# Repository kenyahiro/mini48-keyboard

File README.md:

# このキーボードについて
このキーボードは 19mmピッチ 48キーのロープロファイルキーボードです。
キースイッチは [kailh choc V1用ソケット](https://www.kailhswitch.com/mechanical-keyboard-switches/box-switches/choc-type-hot-swap-socket.html) を使用します。

マイコンには [AE-RP2040](https://akizukidenshi.com/catalog/g/g117542/) を使用します。

ファームウェアは [kmk_firmware](https://github.com/KMKfw/kmk_firmware) を使います。

# 部品表

| レフデス      | 型名           | 数量   | 備考 |
|------------|--------------|------|---------------------------|
| D1 - D48   | 1N4148W      | 48   |                           |
| SW1 - SW48 | CPG135001S30 | 48   | Choc Type Hot Swap Socket |
| U1         | AE-RP2040    | 1    | RP2040マイコンボード            |

この他に, kailh choc V1キースイッチ、 choc V1用キーキャップが必要です。
また、 基板を固定するためM2の支柱とネジを使います。

# マイコンの動作確認
組み立ての前にマイコンボードの動作確認を行います。
マイコンボードに [CircuitPython](https://circuitpython.org/board/raspberry_pi_pico/) を書き込みます。

書き込み後、 [Thonny](https://thonny.org/)等でCircuitPythonが動いていることを確認します。

# 組み立て

## ダイオードのハンダ付け
はじめに, D1 - D48 のダイオードをハンダ付けします。
アノードとカソードの向きを間違えないように注意してください。

## キーソケットのハンダ付け
次にkailh choc V1用キーソケットをハンダ付けします。
キーソケットには向きがあります。 基板のシルクを参考にして、間違えないようにハンダ付けしてください。

## マイコンボードの取り付け
マイコンボードの取り付け方法は、直付け または ピンソケット の選択ができます。

直付けの場合、キーボード裏の厚みを薄くできます。しかし、マイコンボードが故障したときに交換が難しくなります。

ピンソケットを使用した場合、キーボード裏の厚みがピンソケット分増加します。マイコンボードの交換は容易です。

### マイコンボードの組み立て

マイコンボードに 細ピンヘッダ(AE-RP2040付属) または [基板用リードフレーム](https://akizukidenshi.com/catalog/g/g114883/) をハンダ付けします。

細ピンヘッダをハンダ付けする場合、 ブレッドボードを使うとハンダ付けしやすいです。

リードフレームをハンダ付けする場合、 垂直になるようにハンダ付けします。まず1ピンだけ仮止めして、角度を調整します。
垂直になったら、残りのピンをハンダ付けします。

念のため、マイコンボードの裏側に[ポリイミドテープ](https://akizukidenshi.com/catalog/r/rpolyimid/)を貼って絶縁します。

### マイコンボードの取り付け(直付けの場合)
マイコンボードの取り付け前に、ダイオードとキーソケットの向き、ハンダ不良が無いことを確認します。
特に、 マイコンボードの下になる D35, D36, SW35, SW36 は注意して確認します。

U1のスルーホールにマイコンボードを刺し込みます。マイコンボードの裏側とダイオード、キーソケットが接触していないことを確認します。

マイコンボードのハンダ付けをします。まず、1つのピンをハンダ付けして仮止めします。
マイコンボードが水平になっていることを確認します。水平でない場合、ハンダゴデで仮止めしたピンのハンダを温めて、水平になるように修正します。

仮止めでマイコンボードが水平になっていることを確認できたら、残りのピンをハンダ付けします。

### マイコンボードの取り付け(ソケットの場合)
[ピンソケット](https://akizukidenshi.com/catalog/g/g100241/)はマイコンボードのピン数に合せてカットします。

基板にピンソケットをハンダ付けします。ピンソケットは垂直になるようにハンダ付けします。まず1ピンだけ仮止めして、角度を調整します。
垂直になったら、残りのピンをハンダ付けします。

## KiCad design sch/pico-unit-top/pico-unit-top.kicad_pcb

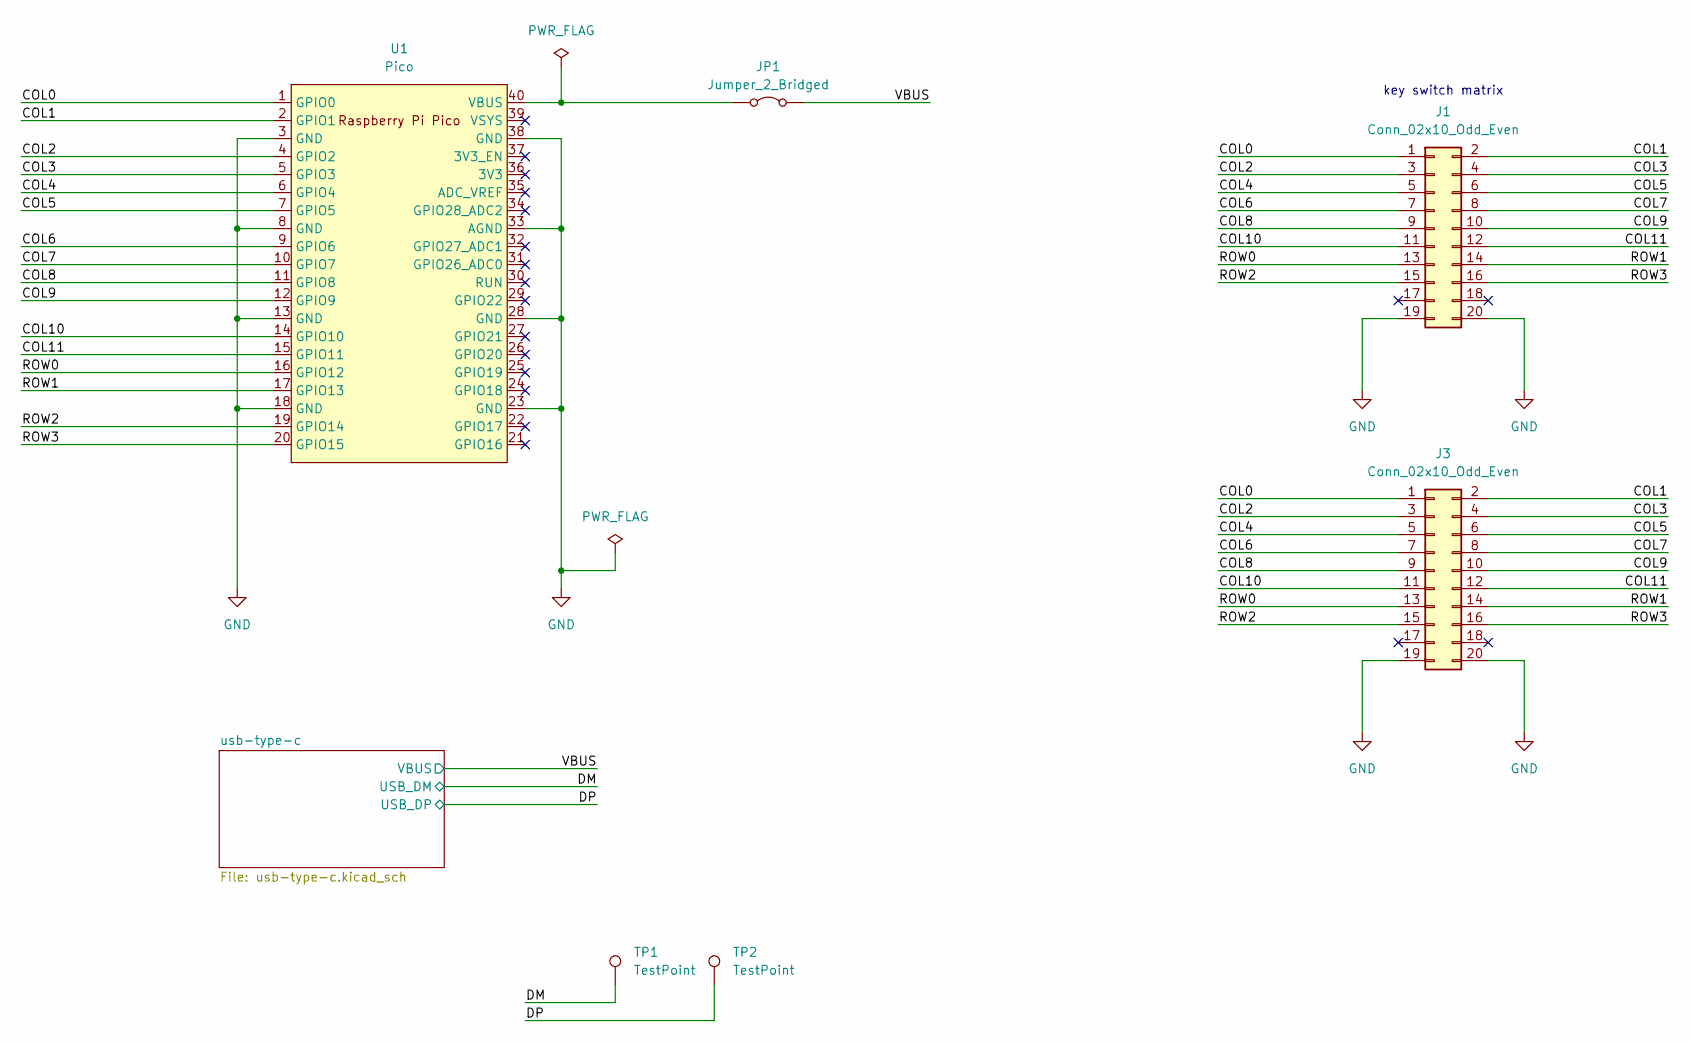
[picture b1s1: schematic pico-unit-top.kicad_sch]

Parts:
J1: Conn_02x10_Odd_Even; PinSocket_2x10_P2.54mm_Horizontal
J3: Conn_02x10_Odd_Even; PinSocket_2x10_P2.54mm_Vertical
JP1: Jumper_2_Bridged; SolderJumper-2_P1.3mm_Bridged_RoundedPad1.0x1.5mm
TP1, TP2: TestPoint; TestPoint_THTPad_2.0x2.0mm_Drill1.0mm
U1: Pico; pico_no_dbg_smd_th_p0.85

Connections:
/COL0: J1.1, J3.1, U1.1 (GPIO0)
/COL1: J1.2, J3.2, U1.2 (GPIO1)
/COL2: J1.3, J3.3, U1.4 (GPIO2)
/COL3: J1.4, J3.4, U1.5 (GPIO3)
/COL4: J1.5, J3.5, U1.6 (GPIO4)
/COL5: J1.6, J3.6, U1.7 (GPIO5)
/COL6: J1.7, J3.7, U1.9 (GPIO6)
/COL7: J1.8, J3.8, U1.10 (GPIO7)
/COL8: J1.9, J3.9, U1.11 (GPIO8)
/COL9: J1.10, J3.10, U1.12 (GPIO9)
/COL10: J1.11, J3.11, U1.14 (GPIO10)
/COL11: J1.12, J3.12, U1.15 (GPIO11)
/DM: TP1.1; also elsewhere on the board
/DP: TP2.1; also elsewhere on the board
/ROW0: J1.13, J3.13, U1.16 (GPIO12)
/ROW1: J1.14, J3.14, U1.17 (GPIO13)
/ROW2: J1.15, J3.15, U1.19 (GPIO14)
/ROW3: J1.16, J3.16, U1.20 (GPIO15)
/VBUS: JP1.2 (B); also elsewhere on the board
GND: J1.19, J1.20, J3.19, J3.20, U1.3 (GND), U1.8 (GND), U1.13 (GND), U1.18 (GND), U1.23 (GND), U1.28 (GND), U1.33 (AGND), U1.38 (GND); also elsewhere on the board
unnamed: JP1.1 (A), U1.40 (VBUS)

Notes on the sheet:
key switch matrix

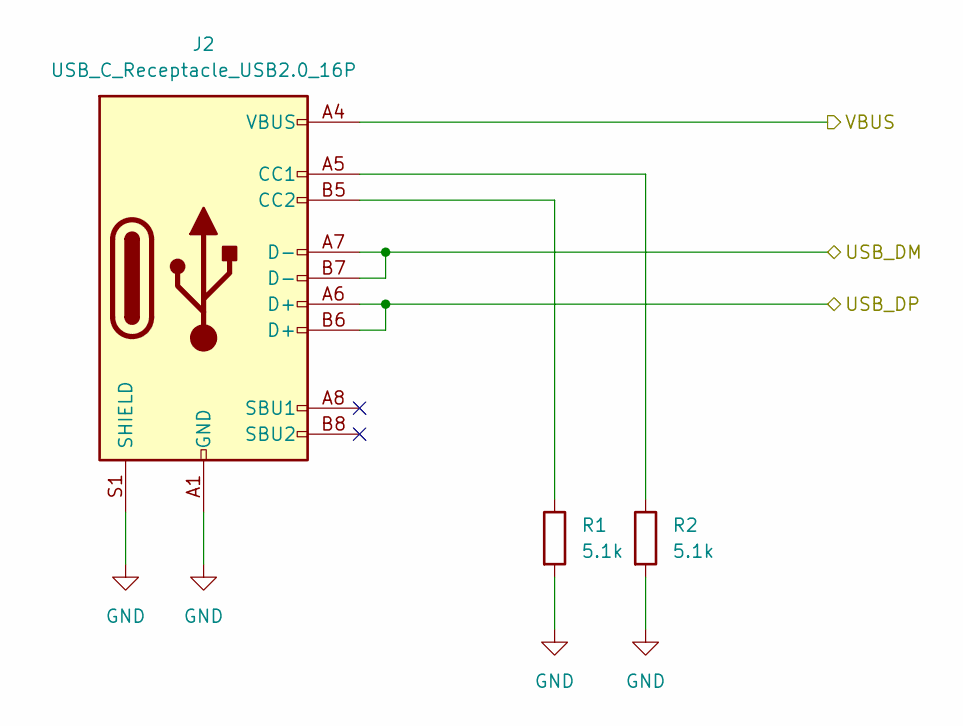
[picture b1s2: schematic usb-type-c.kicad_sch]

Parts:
J2: USB_C_Receptacle_USB2.0_16P; USB_C_Receptacle_G-Switch_GT-USB-7010ASV
R1, R2: 5.1k; R_0603_1608Metric

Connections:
/DM: J2.A7 (D-), J2.B7 (D-); also elsewhere on the board
/DP: J2.A6 (D+), J2.B6 (D+); also elsewhere on the board
/VBUS: J2.A4 (VBUS), J2.A9 (VBUS), J2.B4 (VBUS), J2.B9 (VBUS); also elsewhere on the board
GND: J2.A1 (GND), J2.A12 (GND), J2.B1 (GND), J2.B12 (GND), J2.S1 (SHIELD), R1.2, R2.2; also elsewhere on the board
unnamed: J2.A5 (CC1), R2.1
unnamed: J2.B5 (CC2), R1.1

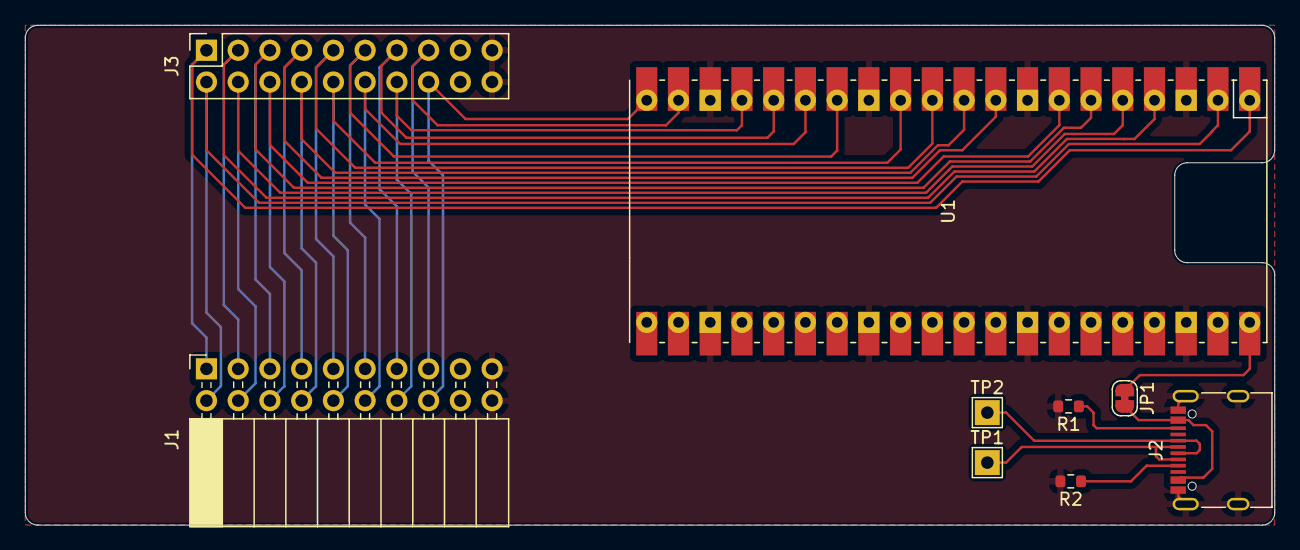
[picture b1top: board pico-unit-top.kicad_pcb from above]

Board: 2 copper layers, 100.0 x 40.0 mm, 9 parts (0 on the bottom side), 23 nets.

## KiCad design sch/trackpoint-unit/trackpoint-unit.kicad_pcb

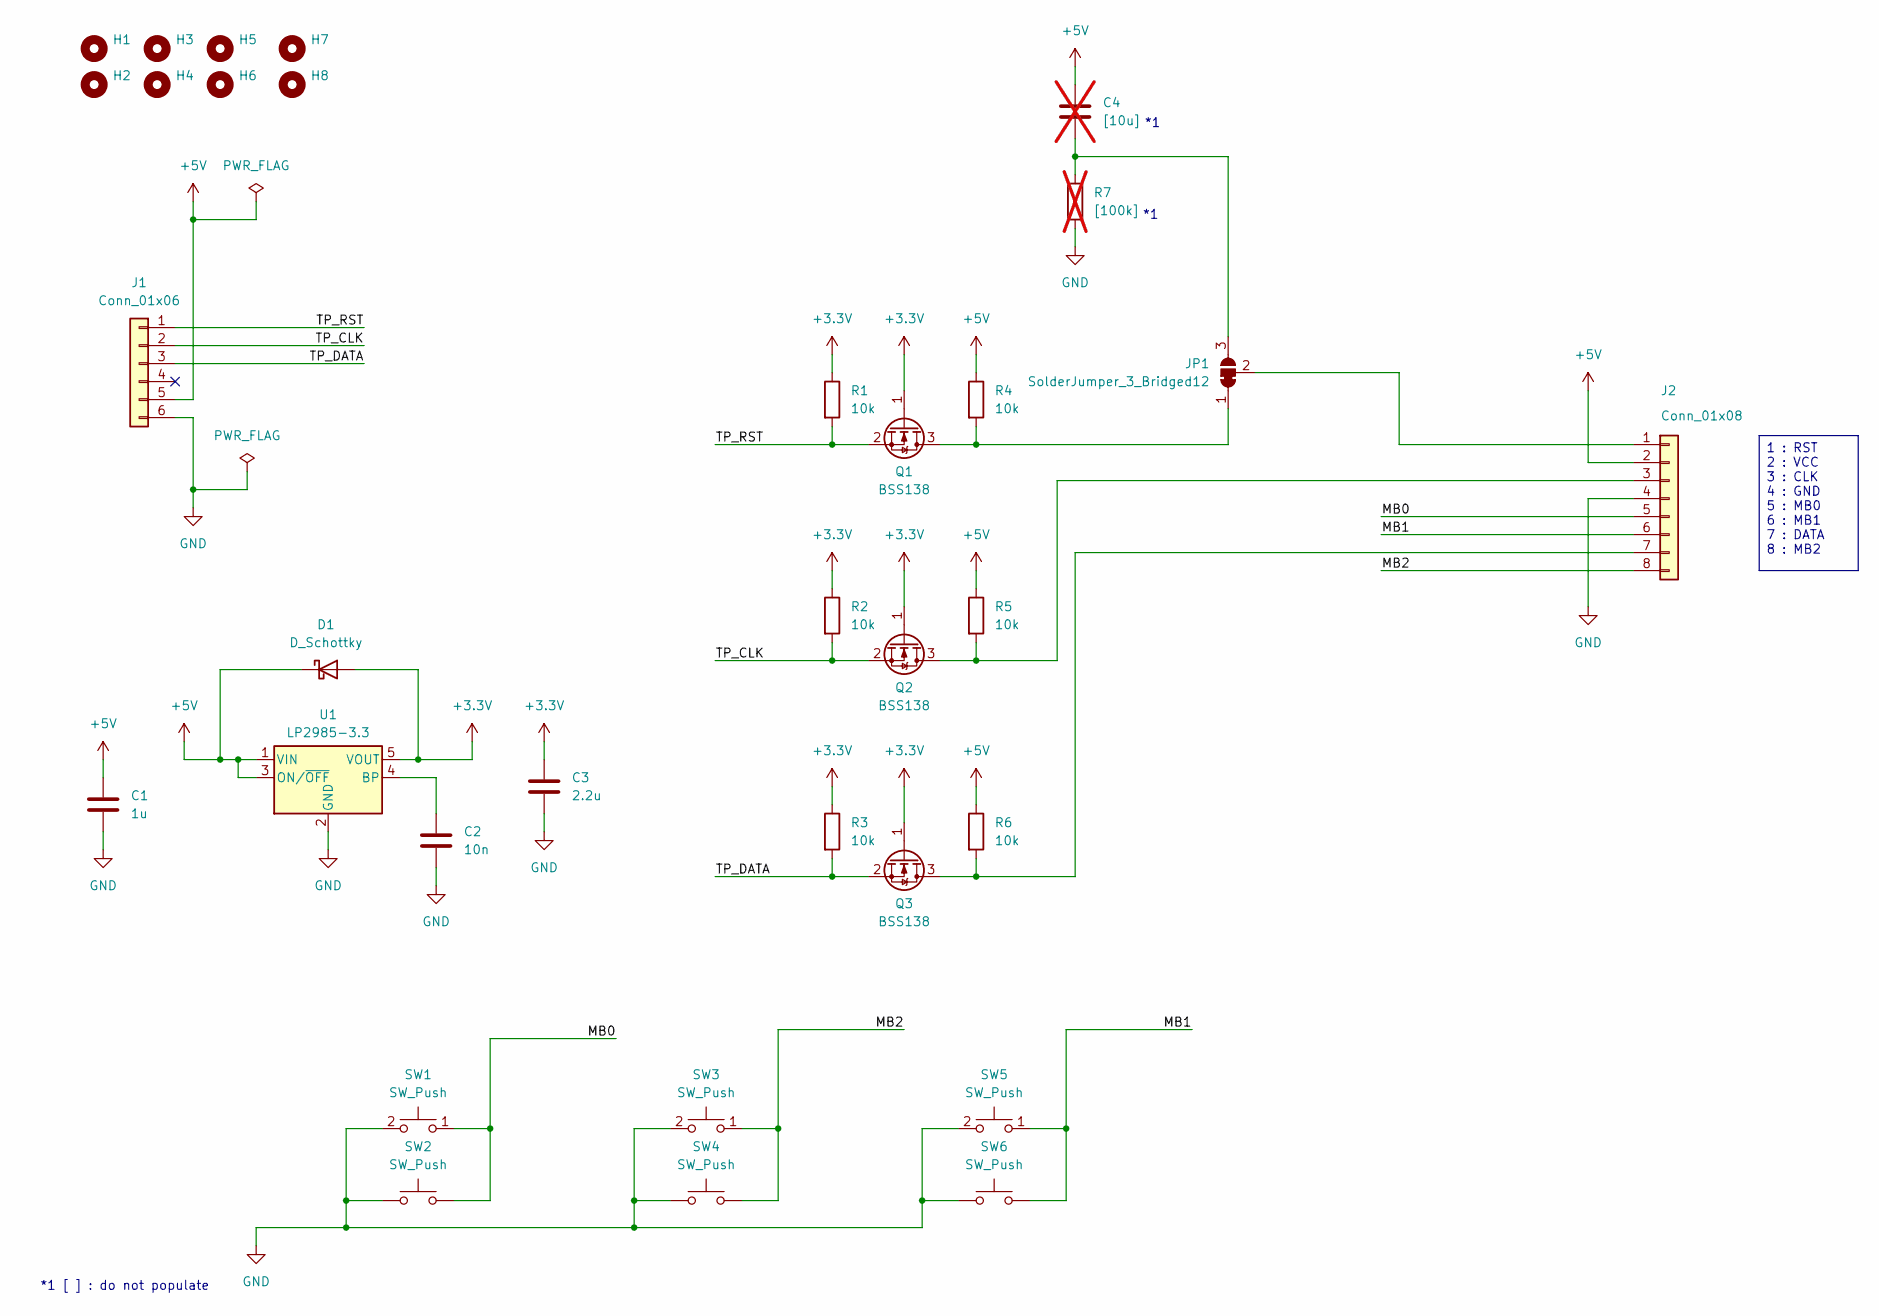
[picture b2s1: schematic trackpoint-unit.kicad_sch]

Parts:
C1: 1u; C_0603_1608Metric
C2: 10n; C_0603_1608Metric
C3: 2.2u; C_0603_1608Metric
C4: [10u]; C_0603_1608Metric; not fitted
D1: D_Schottky; D_SOD-123
H1, H2, H3, H4, H5, H6, H7, H8: MountingHole; MountingHole_2.2mm_M2
J1: Conn_01x06; JST_PH_S6B-PH-K_1x06_P2.00mm_Horizontal
J2: Conn_01x08; JST_PH_S8B-PH-K_1x08_P2.00mm_Horizontal
JP1: SolderJumper_3_Bridged12; SolderJumper-3_P1.3mm_Bridged12_RoundedPad1.0x1.5mm
Q1, Q2, Q3: BSS138; SOT-23
R1, R2, R3, R4, R5, R6: 10k; R_0603_1608Metric
R7: [100k]; R_0603_1608Metric; not fitted
SW1, SW3, SW5: SW_Push; SW_Hotswap_Kailh_MX
SW2, SW4, SW6: SW_Push; SW_Hotswap_Kailh_Choc_V1V2_no_mp
U1: LP2985-3.3; SOT-23-5

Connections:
+3.3V: C3.1, D1.2 (A), Q1.1 (G), Q2.1 (G), Q3.1 (G), R1.1, R2.1, R3.1, U1.5 (VOUT)
+5V: C1.1, C4.1, D1.1 (K), J1.5, J2.2, R4.1, R5.1, R6.1, U1.1 (VIN), U1.3 (ON/~OFF)
/MB0: J2.5, SW1.1, SW2.2
/MB1: J2.6, SW5.1, SW6.2
/MB2: J2.8, SW3.1, SW4.2
/TP_CLK: J1.2, Q2.2 (S), R2.2
/TP_DATA: J1.3, Q3.2 (S), R3.2
/TP_RST: J1.1, Q1.2 (S), R1.2
GND: C1.2, C2.2, C3.2, J1.6, J2.4, R7.2, SW1.2, SW2.1, SW3.2, SW4.1, SW5.2, SW6.1, U1.2 (GND)
unnamed: J2.1, JP1.2 (C)
unnamed: J2.3, Q2.3 (D), R5.2
unnamed: J2.7, Q3.3 (D), R6.2
unnamed: JP1.1 (A), Q1.3 (D), R4.2
unnamed: C4.2, JP1.3 (B), R7.1
unnamed: C2.1, U1.4 (BP)

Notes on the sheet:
*1 [ ] : do not populate
1 : RST 2 : VCC 3 : CLK 4 : GND 5 : MB0 6 : MB1 7 : DATA 8 : MB2

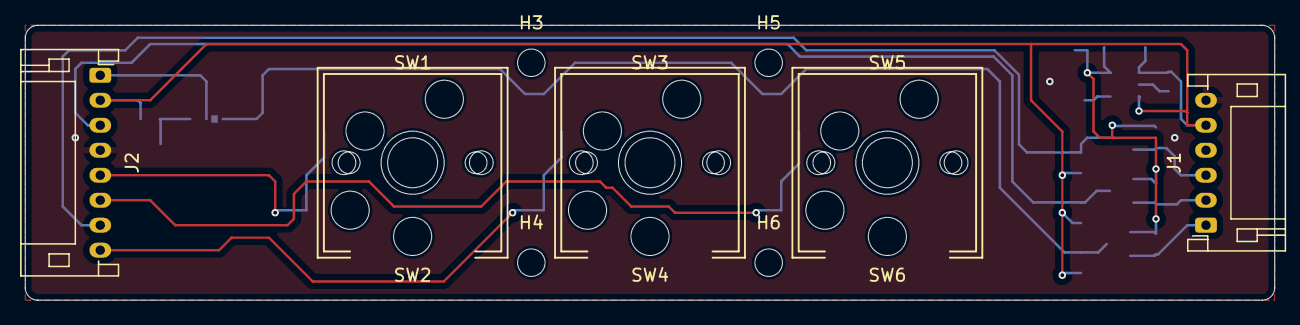
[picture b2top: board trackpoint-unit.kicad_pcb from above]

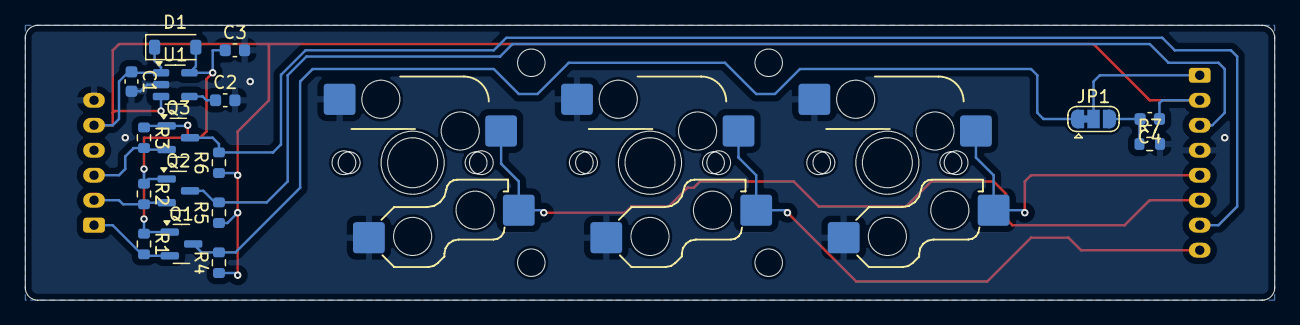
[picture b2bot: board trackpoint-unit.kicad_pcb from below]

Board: 2 copper layers, 100.0 x 22.0 mm, 33 parts (17 on the bottom side), 15 nets.

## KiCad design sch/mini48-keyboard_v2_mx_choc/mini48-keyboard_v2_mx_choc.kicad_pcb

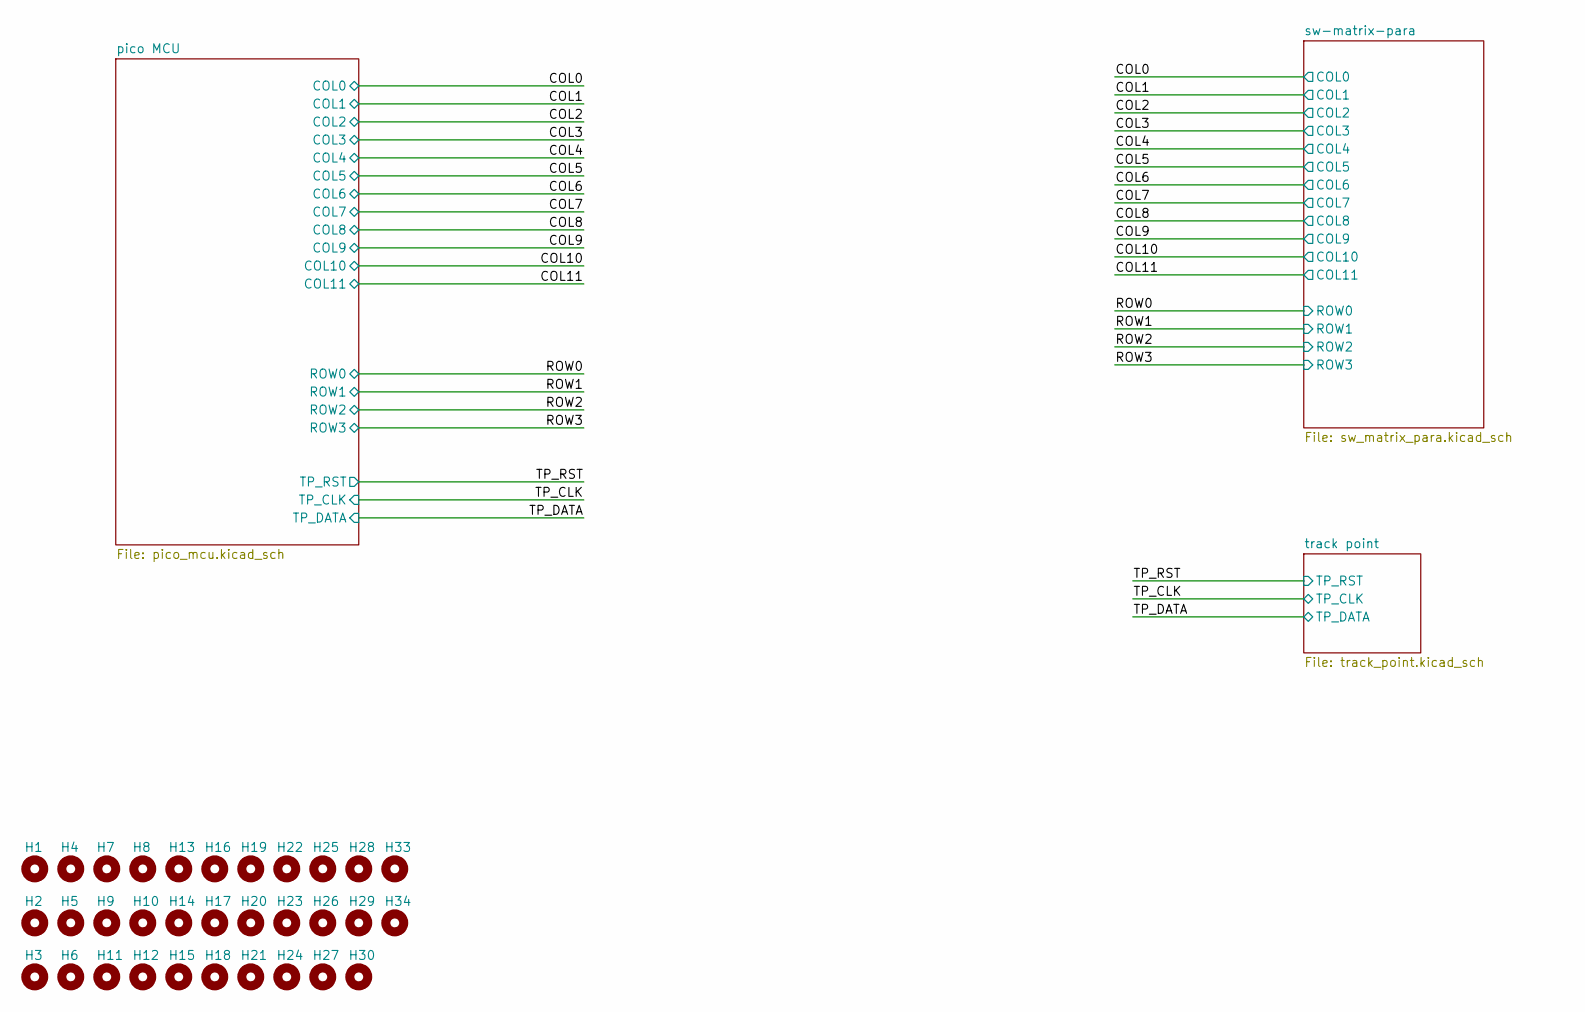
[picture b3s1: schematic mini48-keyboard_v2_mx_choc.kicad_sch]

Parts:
H1, H2, H3, H4, H5, H6, H7, H8, H9, H10, H11, H12, H13, H14, H15, H16, H17, H18, H19, H20, H21, H22, H23, H24, H25, H26, H27, H28, H29, H30, H33, H34: MountingHole; my_MountingHole_3.2mm_M3

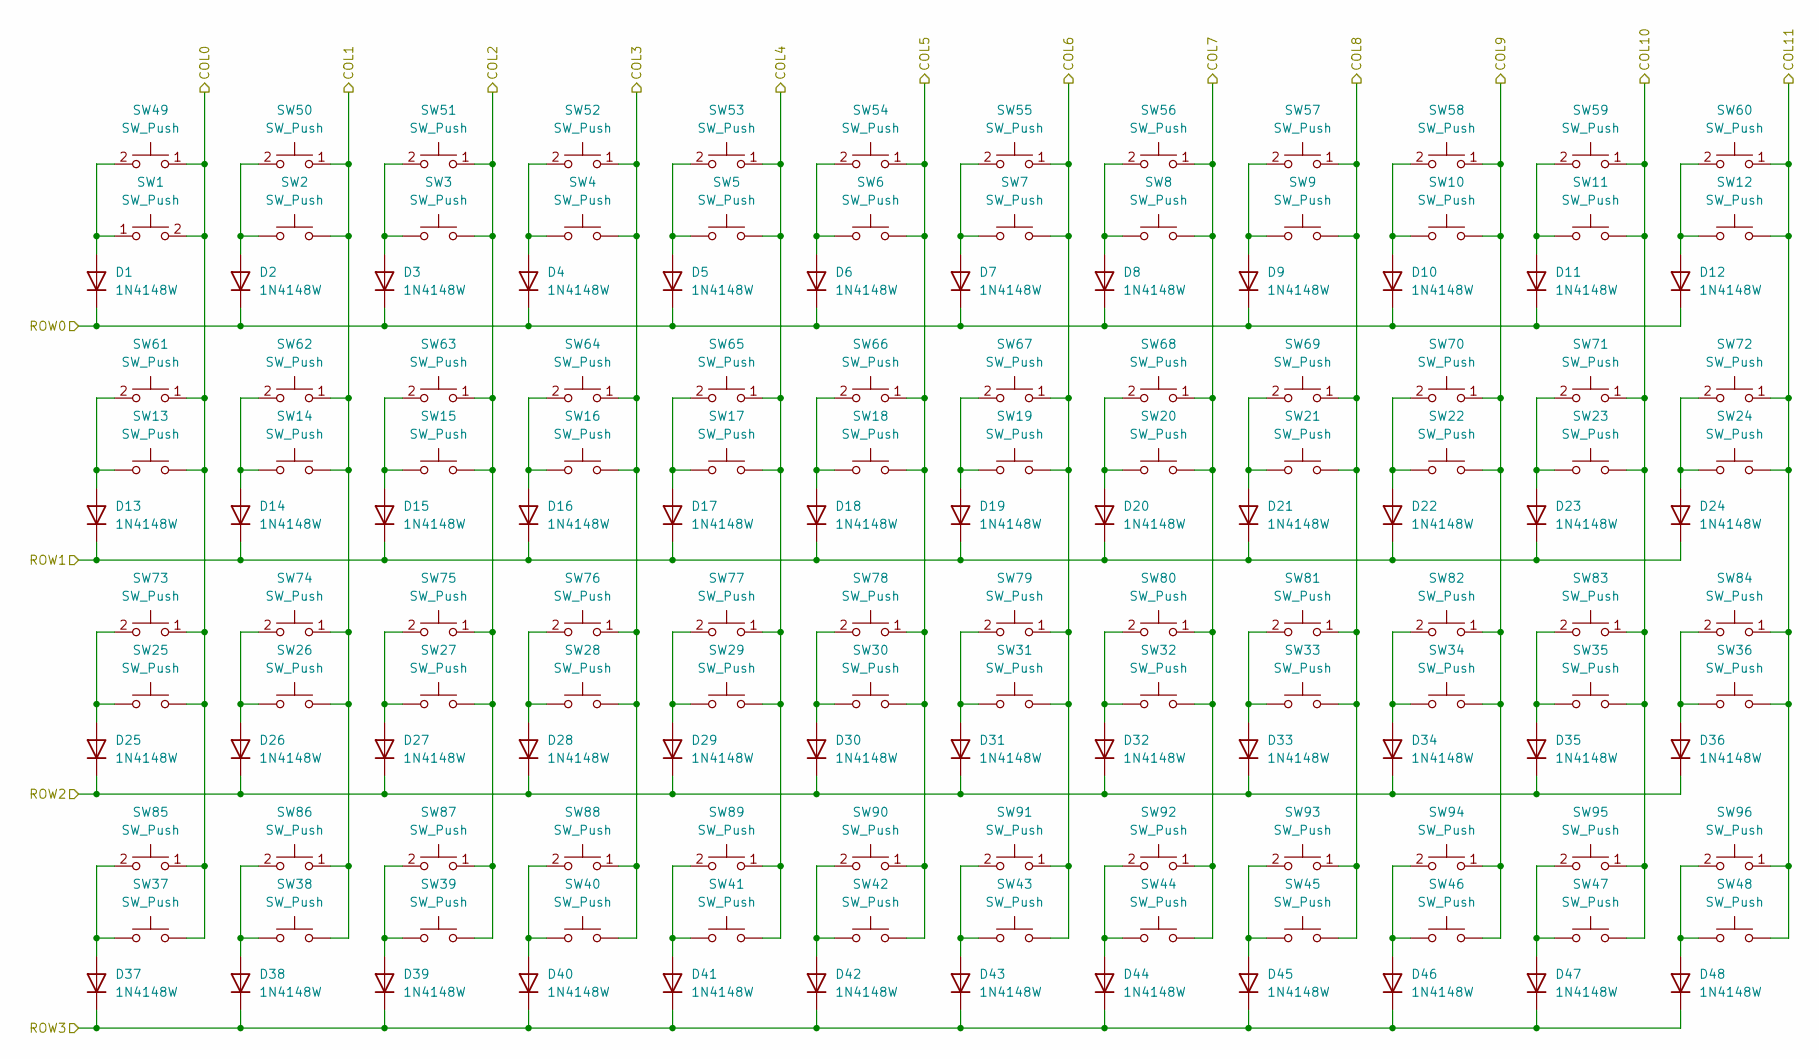
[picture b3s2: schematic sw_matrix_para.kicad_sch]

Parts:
D1, D2, D3, D4, D5, D6, D7, D8, D9, D10, D11, D12, D13, D14, D15, D16, D17, D18, D19, D20, D21, D22, D23, D24, D25, D26, D27, D28, D29, D30, D31, D32, D33, D34, D35, D36, D37, D38, D39, D40, D41, D42, D43, D44, D45, D46, D47, D48: 1N4148W; D_SOD-123
SW1, SW2, SW3, SW4, SW5, SW6, SW7, SW8, SW9, SW10, SW11, SW12, SW13, SW14, SW15, SW16, SW17, SW18, SW19, SW20, SW21, SW22, SW23, SW24, SW25, SW26, SW27, SW28, SW29, SW30, SW31, SW32, SW33, SW34, SW35, SW36, SW37, SW38, SW39, SW40, SW41, SW42, SW43, SW44, SW45, SW46, SW47, SW48: SW_Push; SW_Hotswap_Kailh_Choc_V1V2_no_mp
SW49, SW50, SW51, SW52, SW53, SW54, SW55, SW56, SW57, SW58, SW59, SW60, SW61, SW62, SW63, SW64, SW65, SW66, SW67, SW68, SW69, SW70, SW71, SW72, SW73, SW74, SW75, SW76, SW77, SW78, SW79, SW80, SW81, SW82, SW83, SW84, SW85, SW86, SW87, SW88, SW89, SW90, SW91, SW92, SW93, SW94, SW95, SW96: SW_Push; SW_Hotswap_Kailh_MX

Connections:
/COL0: SW1.2, SW13.2, SW25.2, SW37.2, SW49.1, SW61.1, SW73.1, SW85.1; also elsewhere on the board
/COL1: SW2.2, SW14.2, SW26.2, SW38.2, SW50.1, SW62.1, SW74.1, SW86.1; also elsewhere on the board
/COL2: SW3.2, SW15.2, SW27.2, SW39.2, SW51.1, SW63.1, SW75.1, SW87.1; also elsewhere on the board
/COL3: SW4.2, SW16.2, SW28.2, SW40.2, SW52.1, SW64.1, SW76.1, SW88.1; also elsewhere on the board
/COL4: SW5.2, SW17.2, SW29.2, SW41.2, SW53.1, SW65.1, SW77.1, SW89.1; also elsewhere on the board
/COL5: SW6.2, SW18.2, SW30.2, SW42.2, SW54.1, SW66.1, SW78.1, SW90.1; also elsewhere on the board
/COL6: SW7.2, SW19.2, SW31.2, SW43.2, SW55.1, SW67.1, SW79.1, SW91.1; also elsewhere on the board
/COL7: SW8.2, SW20.2, SW32.2, SW44.2, SW56.1, SW68.1, SW80.1, SW92.1; also elsewhere on the board
/COL8: SW9.2, SW21.2, SW33.2, SW45.2, SW57.1, SW69.1, SW81.1, SW93.1; also elsewhere on the board
/COL9: SW10.2, SW22.2, SW34.2, SW46.2, SW58.1, SW70.1, SW82.1, SW94.1; also elsewhere on the board
/COL10: SW11.2, SW23.2, SW35.2, SW47.2, SW59.1, SW71.1, SW83.1, SW95.1; also elsewhere on the board
/COL11: SW12.2, SW24.2, SW36.2, SW48.2, SW60.1, SW72.1, SW84.1, SW96.1; also elsewhere on the board
/ROW0: D1.1 (K), D2.1 (K), D3.1 (K), D4.1 (K), D5.1 (K), D6.1 (K), D7.1 (K), D8.1 (K), D9.1 (K), D10.1 (K), D11.1 (K), D12.1 (K); also elsewhere on the board
/ROW1: D13.1 (K), D14.1 (K), D15.1 (K), D16.1 (K), D17.1 (K), D18.1 (K), D19.1 (K), D20.1 (K), D21.1 (K), D22.1 (K), D23.1 (K), D24.1 (K); also elsewhere on the board
/ROW2: D25.1 (K), D26.1 (K), D27.1 (K), D28.1 (K), D29.1 (K), D30.1 (K), D31.1 (K), D32.1 (K), D33.1 (K), D34.1 (K), D35.1 (K), D36.1 (K); also elsewhere on the board
/ROW3: D37.1 (K), D38.1 (K), D39.1 (K), D40.1 (K), D41.1 (K), D42.1 (K), D43.1 (K), D44.1 (K), D45.1 (K), D46.1 (K), D47.1 (K), D48.1 (K); also elsewhere on the board
unnamed: D1.2 (A), SW1.1, SW49.2
unnamed: D2.2 (A), SW2.1, SW50.2
unnamed: D3.2 (A), SW3.1, SW51.2
unnamed: D4.2 (A), SW4.1, SW52.2
unnamed: D5.2 (A), SW5.1, SW53.2
unnamed: D6.2 (A), SW6.1, SW54.2
unnamed: D7.2 (A), SW7.1, SW55.2
unnamed: D8.2 (A), SW8.1, SW56.2
unnamed: D9.2 (A), SW9.1, SW57.2
unnamed: D10.2 (A), SW10.1, SW58.2
unnamed: D11.2 (A), SW11.1, SW59.2
unnamed: D12.2 (A), SW12.1, SW60.2
unnamed: D13.2 (A), SW13.1, SW61.2
unnamed: D14.2 (A), SW14.1, SW62.2
unnamed: D15.2 (A), SW15.1, SW63.2
unnamed: D16.2 (A), SW16.1, SW64.2
unnamed: D17.2 (A), SW17.1, SW65.2
unnamed: D18.2 (A), SW18.1, SW66.2
unnamed: D19.2 (A), SW19.1, SW67.2
unnamed: D20.2 (A), SW20.1, SW68.2
unnamed: D21.2 (A), SW21.1, SW69.2
unnamed: D22.2 (A), SW22.1, SW70.2
unnamed: D23.2 (A), SW23.1, SW71.2
unnamed: D24.2 (A), SW24.1, SW72.2
unnamed: D25.2 (A), SW25.1, SW73.2
unnamed: D26.2 (A), SW26.1, SW74.2
unnamed: D27.2 (A), SW27.1, SW75.2
unnamed: D28.2 (A), SW28.1, SW76.2
unnamed: D29.2 (A), SW29.1, SW77.2
unnamed: D30.2 (A), SW30.1, SW78.2
unnamed: D31.2 (A), SW31.1, SW79.2
unnamed: D32.2 (A), SW32.1, SW80.2
unnamed: D33.2 (A), SW33.1, SW81.2
unnamed: D34.2 (A), SW34.1, SW82.2
unnamed: D35.2 (A), SW35.1, SW83.2
unnamed: D36.2 (A), SW36.1, SW84.2
unnamed: D37.2 (A), SW37.1, SW85.2
unnamed: D38.2 (A), SW38.1, SW86.2
unnamed: D39.2 (A), SW39.1, SW87.2
unnamed: D40.2 (A), SW40.1, SW88.2
unnamed: D41.2 (A), SW41.1, SW89.2
unnamed: D42.2 (A), SW42.1, SW90.2
unnamed: D43.2 (A), SW43.1, SW91.2
unnamed: D44.2 (A), SW44.1, SW92.2
unnamed: D45.2 (A), SW45.1, SW93.2
unnamed: D46.2 (A), SW46.1, SW94.2
unnamed: D47.2 (A), SW47.1, SW95.2
unnamed: D48.2 (A), SW48.1, SW96.2

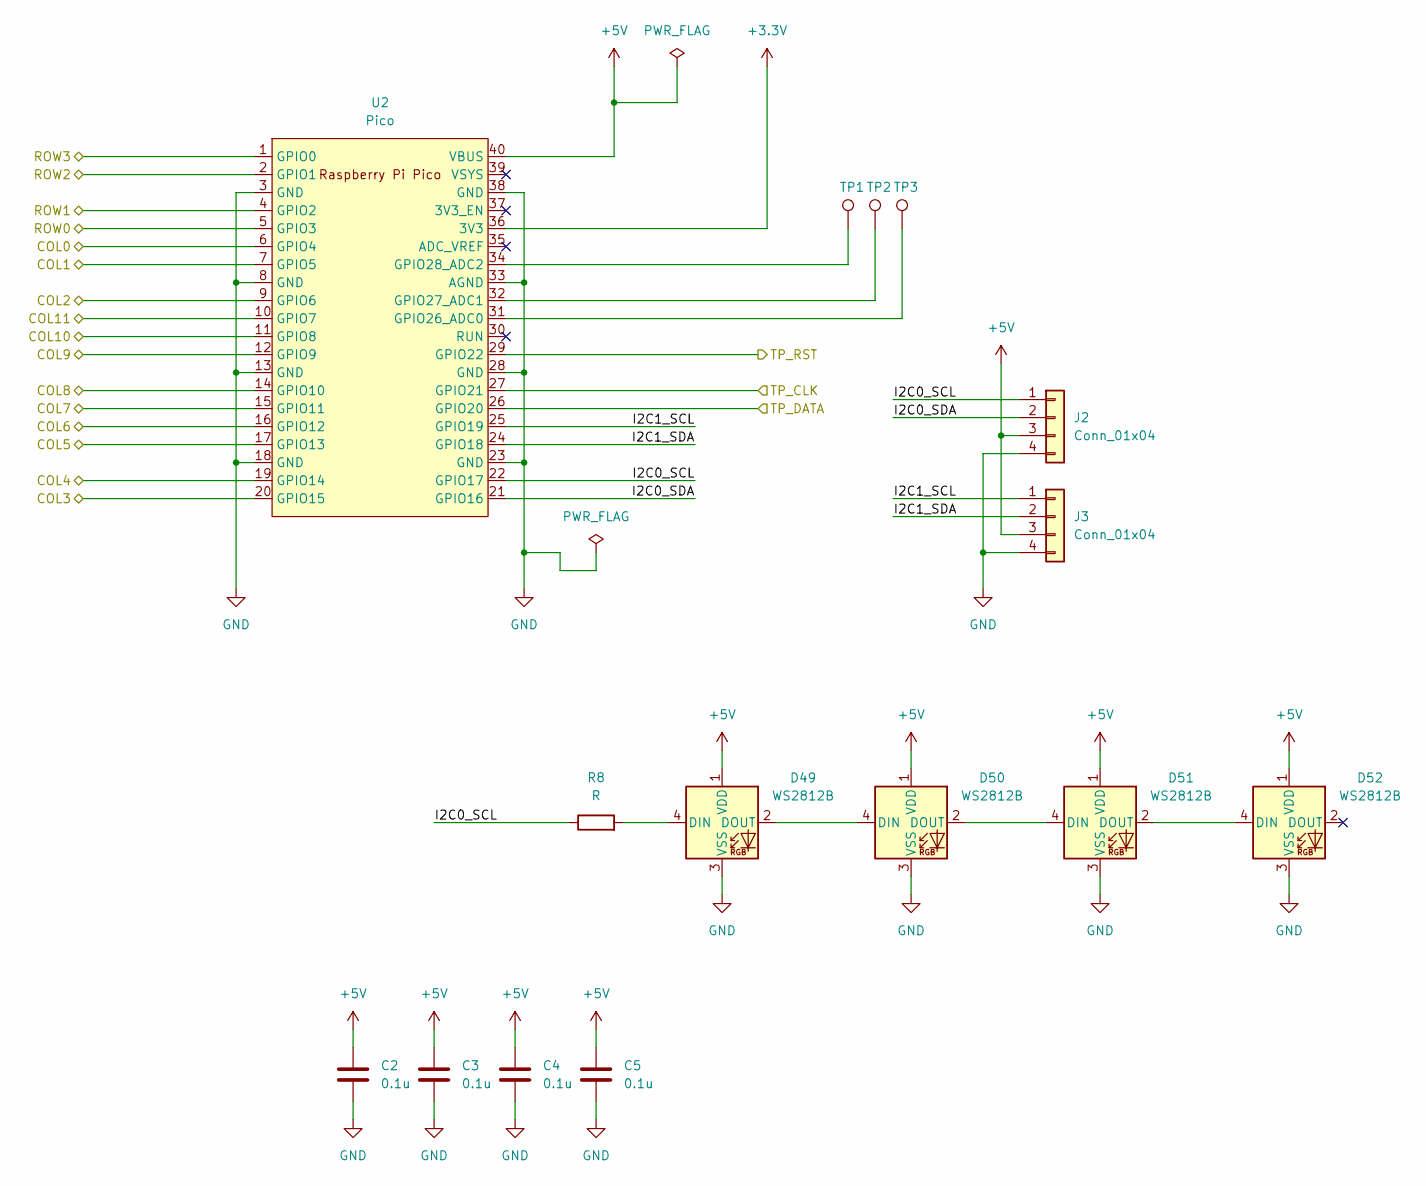
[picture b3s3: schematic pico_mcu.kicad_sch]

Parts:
C2, C3, C4, C5: 0.1u; C_0603_1608Metric
D49, D50, D51, D52: WS2812B; LED_WS2812B_PLCC4_5.0x5.0mm_P3.2mm
J2, J3: Conn_01x04; JST_PH_S4B-PH-K_1x04_P2.00mm_Horizontal
R8: R; R_0603_1608Metric
TP1, TP2, TP3: TestPoint; TestPoint_Pad_D1.0mm
U2: Pico; pico_no_dbg_th_p0.85

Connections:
+3.3V: U2.36 (3V3); also elsewhere on the board
+5V: C2.1, C3.1, C4.1, C5.1, D49.1 (VDD), D50.1 (VDD), D51.1 (VDD), D52.1 (VDD), J2.3, J3.3, U2.40 (VBUS); also elsewhere on the board
/COL0: U2.6 (GPIO4); also elsewhere on the board
/COL1: U2.7 (GPIO5); also elsewhere on the board
/COL2: U2.9 (GPIO6); also elsewhere on the board
/COL3: U2.20 (GPIO15); also elsewhere on the board
/COL4: U2.19 (GPIO14); also elsewhere on the board
/COL5: U2.17 (GPIO13); also elsewhere on the board
/COL6: U2.16 (GPIO12); also elsewhere on the board
/COL7: U2.15 (GPIO11); also elsewhere on the board
/COL8: U2.14 (GPIO10); also elsewhere on the board
/COL9: U2.12 (GPIO9); also elsewhere on the board
/COL10: U2.11 (GPIO8); also elsewhere on the board
/COL11: U2.10 (GPIO7); also elsewhere on the board
/ROW0: U2.5 (GPIO3); also elsewhere on the board
/ROW1: U2.4 (GPIO2); also elsewhere on the board
/ROW2: U2.2 (GPIO1); also elsewhere on the board
/ROW3: U2.1 (GPIO0); also elsewhere on the board
/TP_CLK: U2.27 (GPIO21); also elsewhere on the board
/TP_DATA: U2.26 (GPIO20); also elsewhere on the board
/TP_RST: U2.29 (GPIO22); also elsewhere on the board
/pico MCU/I2C0_SCL: J2.1, R8.1, U2.22 (GPIO17)
/pico MCU/I2C0_SDA: J2.2, U2.21 (GPIO16)
/pico MCU/I2C1_SCL: J3.1, U2.25 (GPIO19)
/pico MCU/I2C1_SDA: J3.2, U2.24 (GPIO18)
GND: C2.2, C3.2, C4.2, C5.2, D49.3 (VSS), D50.3 (VSS), D51.3 (VSS), D52.3 (VSS), J2.4, J3.4, U2.3 (GND), U2.8 (GND), U2.13 (GND), U2.18 (GND), U2.23 (GND), U2.28 (GND), U2.33 (AGND), U2.38 (GND); also elsewhere on the board
unnamed: D49.4 (DIN), R8.2
unnamed: D49.2 (DOUT), D50.4 (DIN)
unnamed: D50.2 (DOUT), D51.4 (DIN)
unnamed: D51.2 (DOUT), D52.4 (DIN)
unnamed: TP3.1, U2.31 (GPIO26_ADC0)
unnamed: TP2.1, U2.32 (GPIO27_ADC1)
unnamed: TP1.1, U2.34 (GPIO28_ADC2)

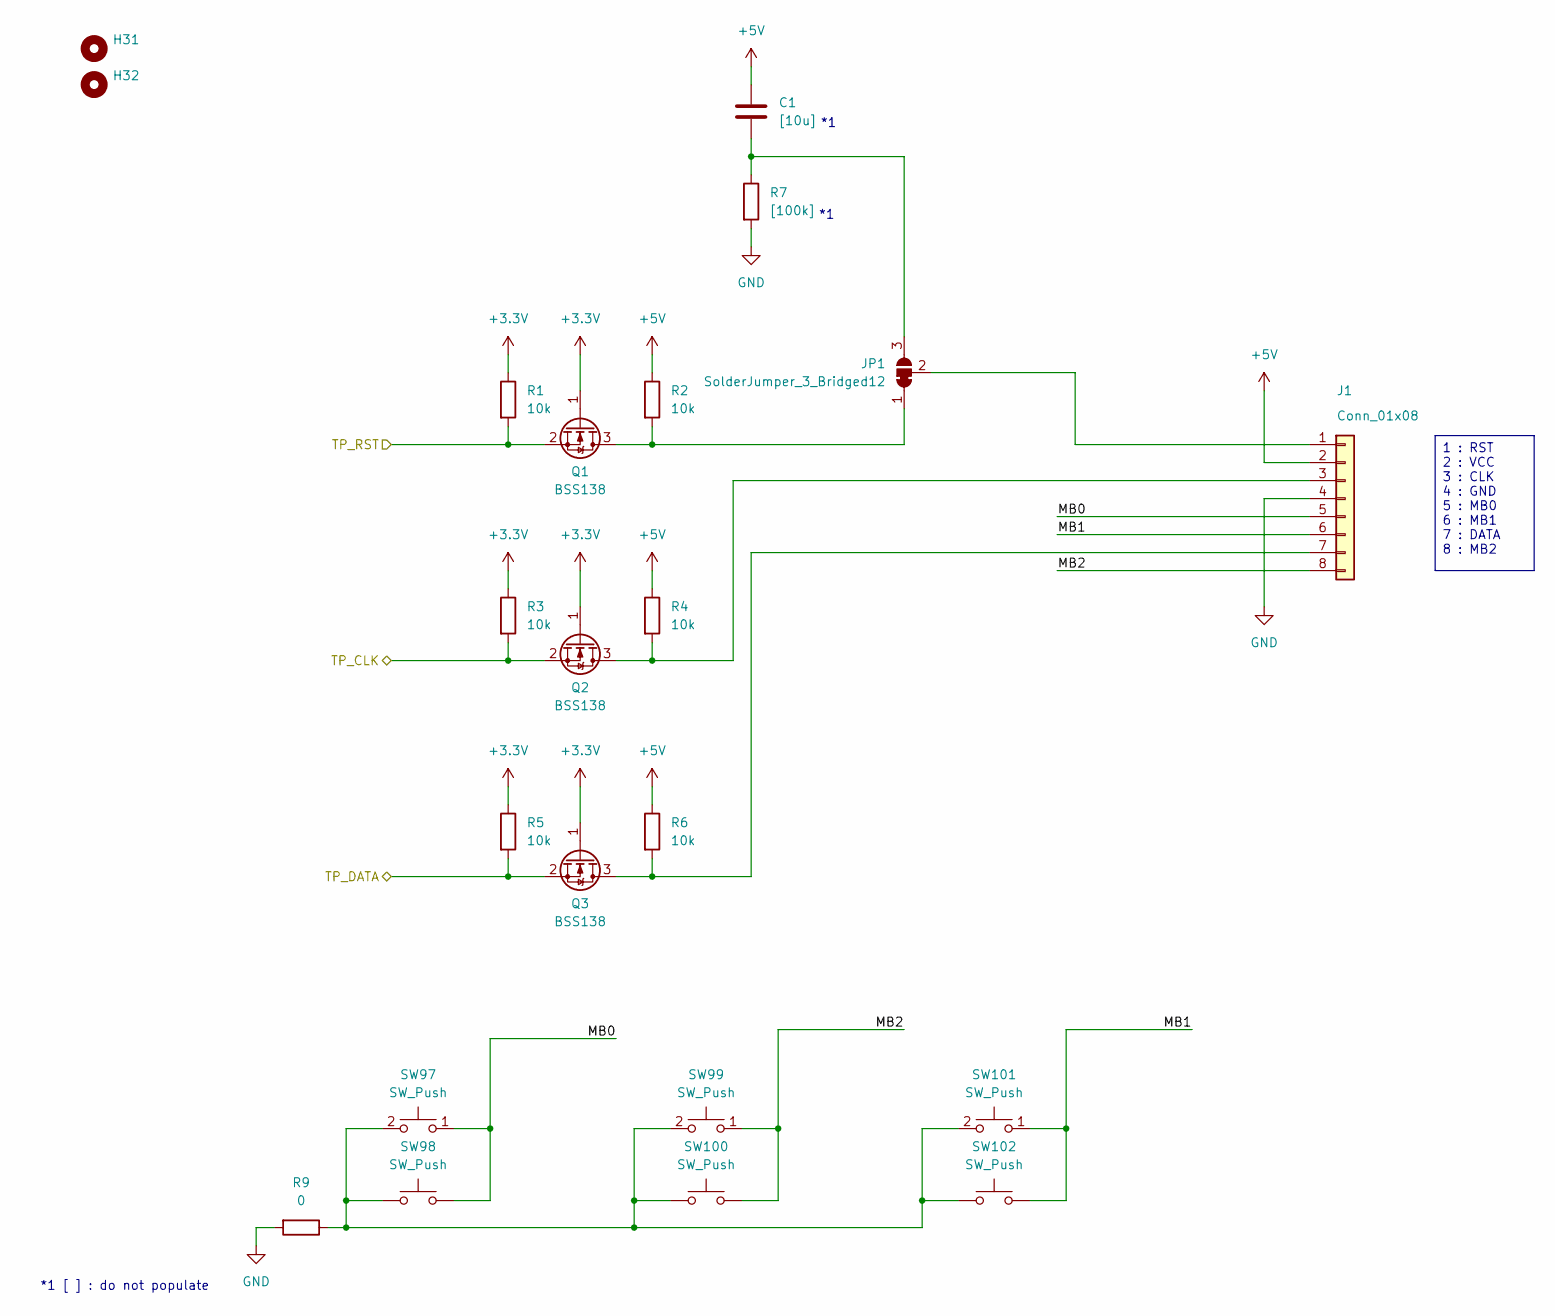
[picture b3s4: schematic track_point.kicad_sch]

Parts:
C1: [10u]; C_0603_1608Metric
H31, H32: MountingHole; MountingHole_2.2mm_M2
J1: Conn_01x08; JST_PH_B8B-PH-K_1x08_P2.00mm_Vertical
JP1: SolderJumper_3_Bridged12; SolderJumper-3_P1.3mm_Bridged12_RoundedPad1.0x1.5mm
Q1, Q2, Q3: BSS138; SOT-23
R1, R2, R3, R4, R5, R6: 10k; R_0603_1608Metric
R7: [100k]; R_0603_1608Metric
R9: 0; R_0603_1608Metric
SW97, SW99, SW101: SW_Push; SW_Hotswap_Kailh_MX
SW98, SW100, SW102: SW_Push; SW_Hotswap_Kailh_Choc_V1V2_no_mp

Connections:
+3.3V: Q1.1 (G), Q2.1 (G), Q3.1 (G), R1.1, R3.1, R5.1; also elsewhere on the board
+5V: C1.1, J1.2, R2.1, R4.1, R6.1; also elsewhere on the board
/TP_CLK: Q2.2 (S), R3.2; also elsewhere on the board
/TP_DATA: Q3.2 (S), R5.2; also elsewhere on the board
/TP_RST: Q1.2 (S), R1.2; also elsewhere on the board
/track point/MB0: J1.5, SW97.1, SW98.2
/track point/MB1: J1.6, SW101.1, SW102.2
/track point/MB2: J1.8, SW99.1, SW100.2
GND: J1.4, R7.2, R9.2; also elsewhere on the board
unnamed: J1.1, JP1.2 (C)
unnamed: J1.3, Q2.3 (D), R4.2
unnamed: J1.7, Q3.3 (D), R6.2
unnamed: JP1.1 (A), Q1.3 (D), R2.2
unnamed: C1.2, JP1.3 (B), R7.1
unnamed: R9.1, SW97.2, SW98.1, SW99.2, SW100.1, SW101.2, SW102.1

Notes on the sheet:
*1 [ ] : do not populate
1 : RST 2 : VCC 3 : CLK 4 : GND 5 : MB0 6 : MB1 7 : DATA 8 : MB2

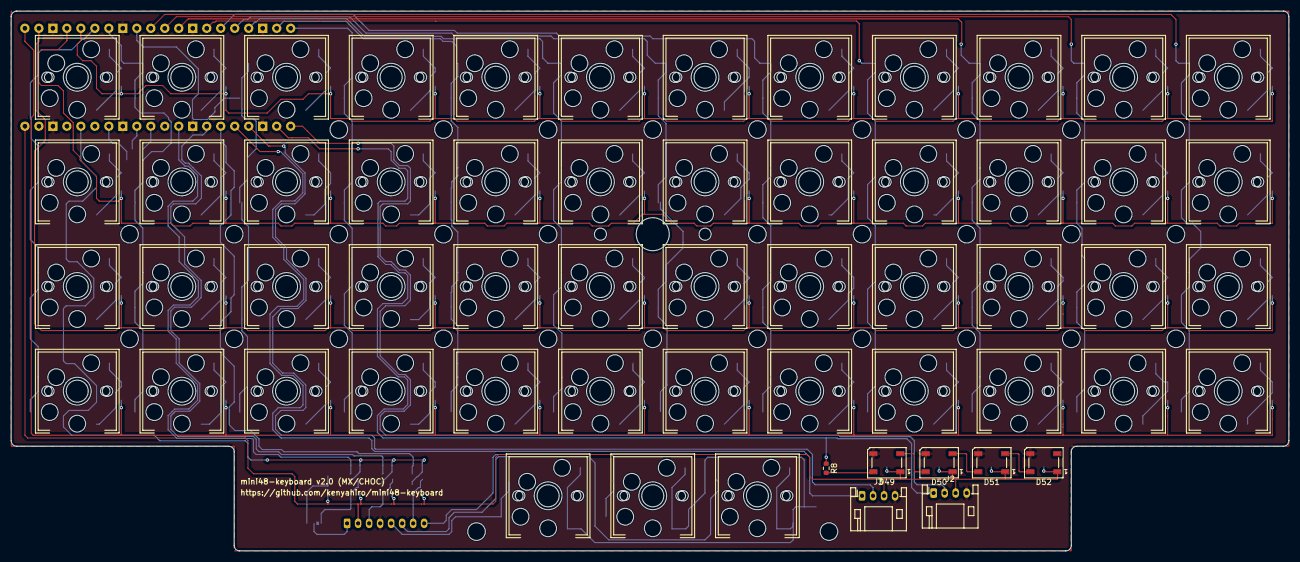
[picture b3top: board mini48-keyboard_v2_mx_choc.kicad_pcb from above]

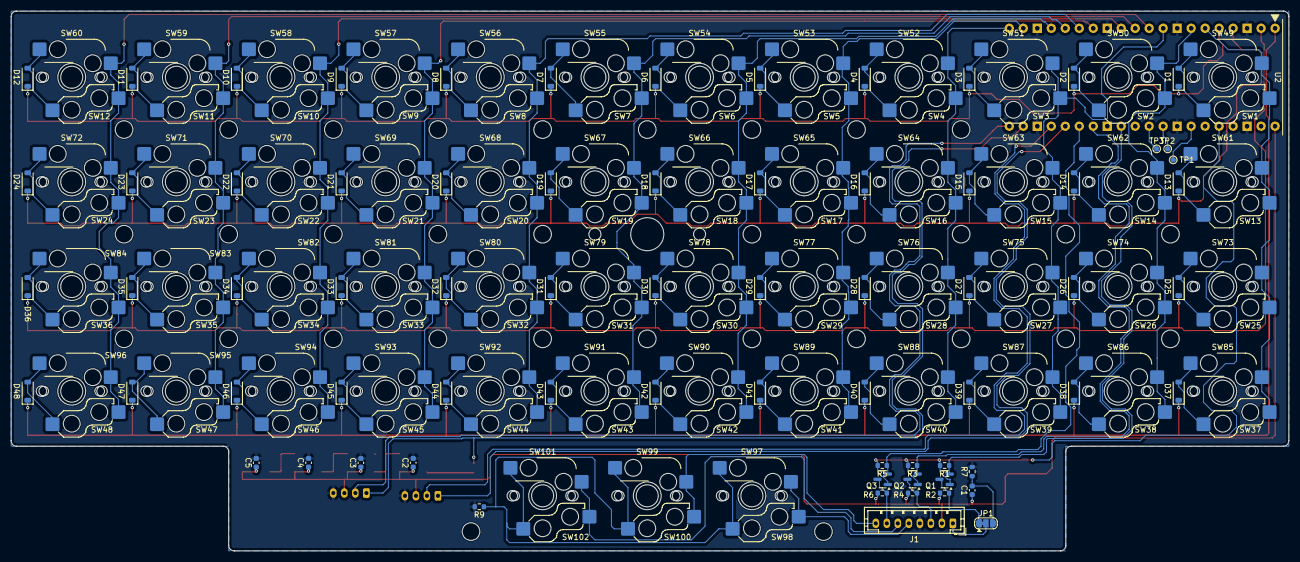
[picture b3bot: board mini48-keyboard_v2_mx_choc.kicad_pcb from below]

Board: 2 copper layers, 232.0 x 98.0 mm, 213 parts (70 on the bottom side), 90 nets.
